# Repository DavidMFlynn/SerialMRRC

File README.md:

# SerialMRRC
 Serial Model Railroad Control

This is a set of PCBs and software to control a model railroad with RS485 data buss.

# Stand Alone Boards
Controller Board, PIC15F15345, 1KB Ram, 224B Flash, 8KW Program memory
Switch Machine, 1 servo, 1 DPDT relay
Switch Machine and Signals, 1 servo, 1 DPDT relay, 5 Signal heads

# Daughter Cards
USB Daughter Board
Input 32 Daughter Bouad, 32 Pull-to-Ground inputs
Output 32 Daughter Board, 32 Open collector Pull-to-Ground outputs
Lighting 8x Transistot Outputs, +12v resistor current limited outputs

Anamation Controller, 8 servos
Block Detector, detects voltage across diode/resistor
Optical Detector, broken beam or reflected beam

# USB Operation
 When a command packet is received from RX2 (USB):
  Source=Master, Destination=Me: Parse and Process the command.
    Send any requested data back to Master on TX2 (USB).
  Source=Master, Destination<>Me: Retransmit on TX1 (RS485)

 When a command packet is received from RX1 (RS485):
  Source=any, Destination=Me: Parse and Process the command. 
     Send any requested data back to the sender on TX1 (RS485).
  Source=any, Destination=Master: Retransmit on TX2 (USB)
  Source=any, Destination= other than Master or Me do nothing.

# Node (w/o USB)
 When a command packet is received from RX1 (RS485):
  Source=any, Destination=Me: Parse and Process the command. 
     Send any requested data back to the sender on TX1 (RS485).
  Source=any, Destination<>Me do nothing.

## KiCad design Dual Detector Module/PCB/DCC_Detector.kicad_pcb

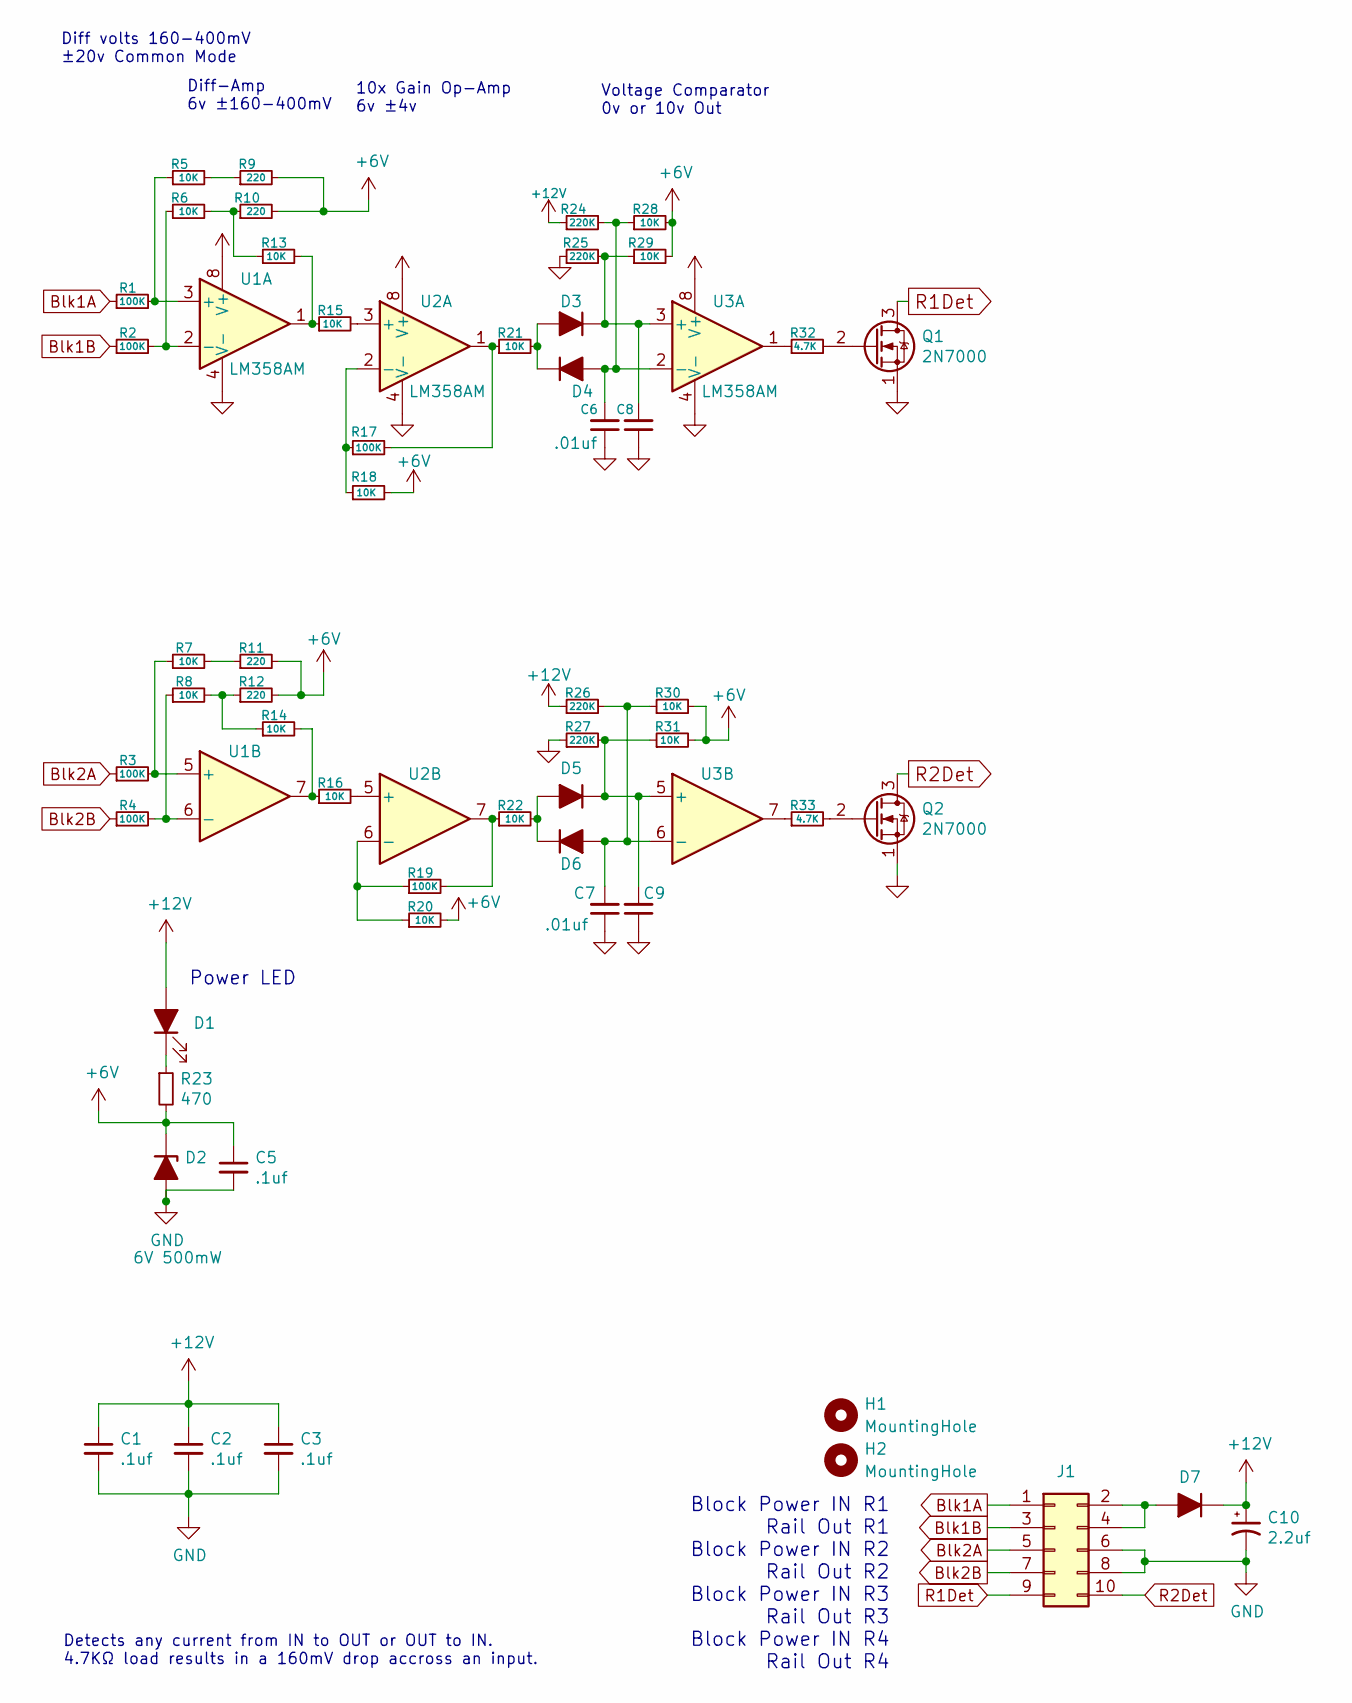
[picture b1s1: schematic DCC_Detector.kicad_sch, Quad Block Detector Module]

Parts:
C1, C2, C3, C5: .1uf; C_0805_2012Metric_Pad1.18x1.45mm_HandSolder
C6, C7, C8, C9: .01uf; C_0805_2012Metric_Pad1.18x1.45mm_HandSolder
C10: 2.2uf; CP_Elec_3x5.3
D1: 1206 LED; LED_1206_3216Metric_Pad1.42x1.75mm_HandSolder
D2: 6V 500mW; D_SMA_Handsoldering
D3, D4, D5, D6: 1N4148W; D_SOD-123
D7: D_ALT; D_SMA_Handsoldering
H1, H2: MountingHole; MountingHole_3.2mm_M3
J1: Conn_02x05_Odd_Even; PinSocket_2x05_P2.54mm_Vertical
Q1, Q2: 2N7000; TO-92_Inline
R1, R2, R3, R4, R17, R19: 100K; R_0805_2012Metric_Pad1.20x1.40mm_HandSolder
R5, R6, R7, R8, R13, R14, R15, R16, R18, R20, R21, R22, R28, R29, R30, R31: 10K; R_0805_2012Metric_Pad1.20x1.40mm_HandSolder
R9, R10, R11, R12: 220; R_0805_2012Metric_Pad1.20x1.40mm_HandSolder
R23: 470; R_0805_2012Metric_Pad1.20x1.40mm_HandSolder
R24, R25, R26, R27: 220K; R_0805_2012Metric_Pad1.20x1.40mm_HandSolder
R32, R33: 4.7K; R_0805_2012Metric_Pad1.20x1.40mm_HandSolder
U1, U2, U3: LM358AM; SOIC-8_3.9x4.9mm_P1.27mm

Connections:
+6V: C5.1, D2.1 (K), R9.2, R10.2, R11.2, R12.2, R18.2, R20.2, R23.2, R28.2, R29.2, R30.2, R31.2
+12V: C1.1, C2.1, C3.1, C10.1, D1.2 (A), D7.1 (K), R24.1, R26.1, U1.8 (V+), U2.8 (V+), U3.8 (V+)
Blk1A: J1.1, R1.1
Blk1B: J1.3, R2.1
Blk2A: J1.5, R3.1
Blk2B: J1.7, R4.1
GND: C1.2, C2.2, C3.2, C5.2, C6.1, C7.1, C8.1, C9.1, C10.2, D2.2 (A), J1.6, J1.8, Q1.1 (S), Q2.1 (S), R25.1, R27.1, U1.4 (V-), U2.4 (V-), U3.4 (V-)
unnamed: D1.1 (K), R23.1
unnamed: D3.2 (A), D4.1 (K), R21.2
unnamed: C8.2, D3.1 (K), R25.2, R29.1, U3.3 (+)
unnamed: C6.2, D4.2 (A), R24.2, R28.1, U3.2 (-)
unnamed: D5.2 (A), D6.1 (K), R22.2
unnamed: C9.2, D5.1 (K), R27.2, R31.1, U3.5 (+)
unnamed: C7.2, D6.2 (A), R26.2, R30.1, U3.6 (-)
unnamed: D7.2 (A), J1.2, J1.4
unnamed: Q1.2 (G), R32.2
unnamed: Q2.2 (G), R33.2
unnamed: R5.2, R9.1
unnamed: R6.2, R10.1, R13.1
unnamed: R7.2, R11.1
unnamed: R8.2, R12.1, R14.1
unnamed: R13.2, R15.1, U1.1
unnamed: R14.2, R16.1, U1.7
unnamed: R17.2, R21.1, U2.1
unnamed: R19.2, R22.1, U2.7
unnamed: R32.1, U3.1
unnamed: R33.1, U3.7
unnamed: R1.2, R5.1, U1.3 (+)
unnamed: R2.2, R6.1, U1.2 (-)
unnamed: R3.2, R7.1, U1.5 (+)
unnamed: R4.2, R8.1, U1.6 (-)
unnamed: R15.2, U2.3 (+)
unnamed: R17.1, R18.1, U2.2 (-)
unnamed: R16.2, U2.5 (+)
unnamed: R19.1, R20.1, U2.6 (-)
R1Det: J1.9, Q1.3 (D)
R2Det: J1.10, Q2.3 (D)

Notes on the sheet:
Detects any current from IN to OUT or OUT to IN. 4.7KΩ load results in a 160mV drop accross an input.
Voltage Comparator 0v or 10v Out
Block Power IN R1 Rail Out R1 Block Power IN R2 Rail Out R2 Block Power IN R3 Rail Out R3 Block Power IN R4 Rail Out R4
Diff-Amp 6v ±160-400mV
10x Gain Op-Amp 6v ±4v
Diff volts 160-400mV ±20v Common Mode
Power LED

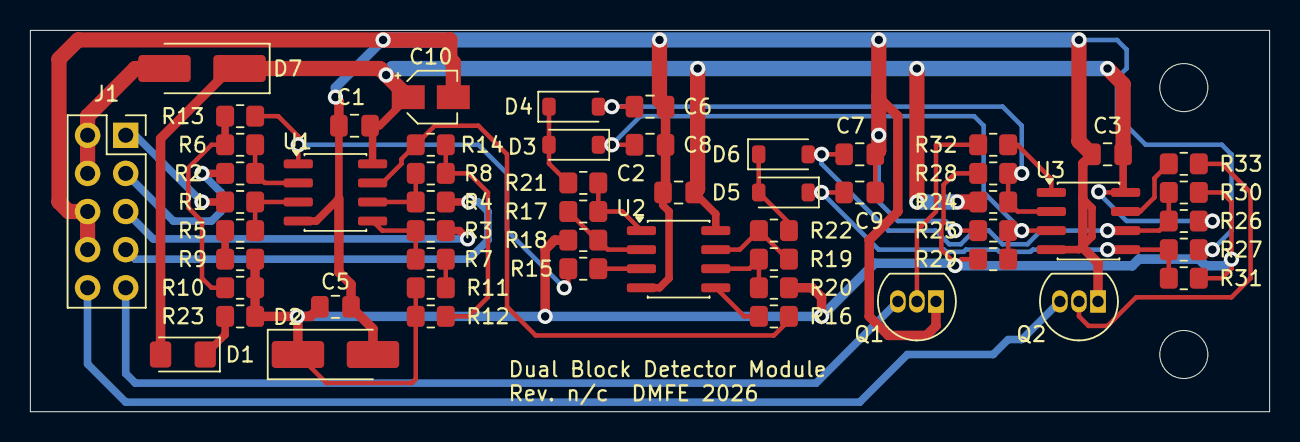
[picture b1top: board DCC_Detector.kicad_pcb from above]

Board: 2 copper layers, 82.6 x 25.4 mm, 57 parts (0 on the bottom side), 37 nets.

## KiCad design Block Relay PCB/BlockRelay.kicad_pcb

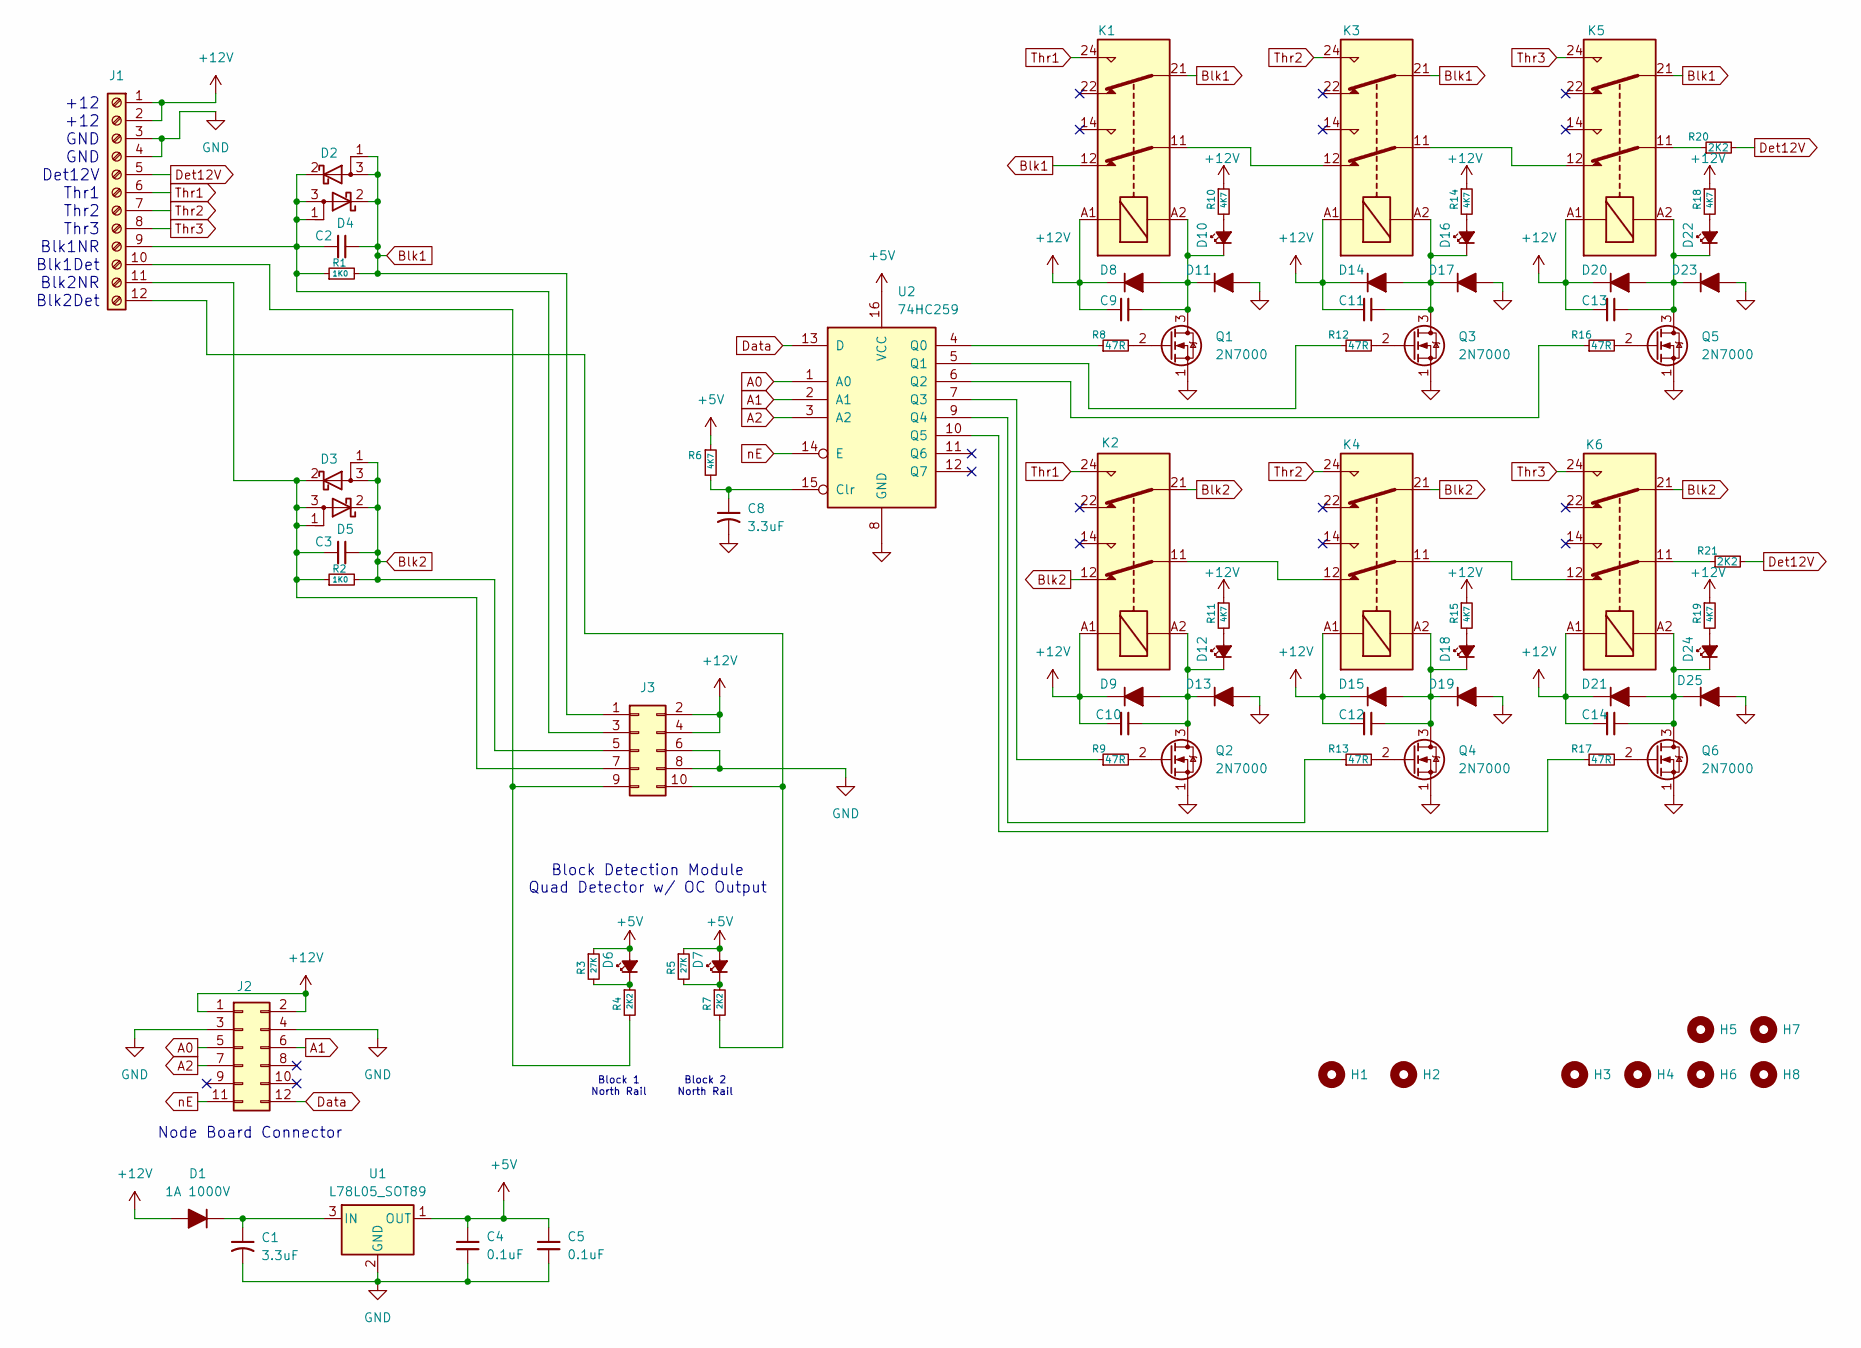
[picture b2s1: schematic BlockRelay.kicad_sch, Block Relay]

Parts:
C1, C8: 3.3uF; C_Radial_D5.0mm_H5.0mm_P2.00mm
C2, C3, C4, C5, C9, C10, C11, C12, C13, C14: 0.1uF; C_0805_2012Metric_Pad1.18x1.45mm_HandSolder
D1, D8, D9, D11, D13, D14, D15, D17, D19, D20, D21, D23, D25: 1A 1000V; D_SMA_Handsoldering
D2, D3, D4, D5: Schottky_AKA DPAK; TO-252-2
D6, D7, D10, D12, D16, D18, D22, D24: Yellow LED; LED_1206_3216Metric_Pad1.42x1.75mm_HandSolder
H1, H2, H3, H4, H5, H6, H7, H8: MountingHole; MountingHole_3.2mm_M3
J1: Screw_Terminal_01x12; TerminalBlock_Phoenix_PT-1,5-12-3.5-H_1x12_P3.50mm_Horizont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
J2: Conn_02x06_Odd_Even; PinHeader_2x06_P2.54mm_Vertical
J3: Conn_02x05_Odd_Even; PinSocket_2x05_P2.54mm_Vertical
K1, K2, K3, K4, K5, K6: Relay_DPDT; Relay_DPDT_Finder_40.52
Q1, Q2, Q3, Q4, Q5, Q6: 2N7000; TO-92_Inline
R1, R2: 1K0; R_0805_2012Metric_Pad1.20x1.40mm_HandSolder
R3, R5: 27K; R_0805_2012Metric_Pad1.20x1.40mm_HandSolder
R4, R7: 2K2; R_0805_2012Metric_Pad1.20x1.40mm_HandSolder
R6, R10, R11, R14, R15, R18, R19: 4K7; R_0805_2012Metric_Pad1.20x1.40mm_HandSolder
R8, R9, R12, R13, R16, R17: 47R; R_0805_2012Metric_Pad1.20x1.40mm_HandSolder
R20, R21: 2K2; R_Axial_DIN0516_L15.5mm_D5.0mm_P20.32mm_Horizontal
U1: L78L05_SOT89; SOT-89-3
U2: 74HC259; SOIC-16_3.9x9.9mm_P1.27mm

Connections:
+5V: C4.1, C5.1, D6.2 (A), D7.2 (A), R3.1, R5.1, R6.1, U1.1 (OUT), U2.16 (VCC)
+12V: C9.1, C10.1, C11.1, C12.1, C13.1, C14.1, D1.2 (A), D8.1 (K), D9.1 (K), D14.1 (K), D15.1 (K), D20.1 (K), D21.1 (K), J1.1, J1.2, J2.1, J2.2, J3.2, J3.4, K1.A1, K2.A1, K3.A1, K4.A1, K5.A1, K6.A1, R10.1, R11.1, R14.1, R15.1, R18.1, R19.1
A0: J2.5, U2.1 (A0)
A1: J2.6, U2.2 (A1)
A2: J2.7, U2.3 (A2)
Blk1: C2.2, D2.1 (A), D2.3 (A), D4.2 (K), J3.1, K1.12, K1.21, K3.21, K5.21, R1.2
Blk2: C3.2, D3.1 (A), D3.3 (A), D5.2 (K), J3.5, K2.12, K2.21, K4.21, K6.21, R2.2
Data: J2.12, U2.13 (D)
Det12V: J1.5, R20.2, R21.2
GND: C1.2, C4.2, C5.2, C8.2, D11.2 (A), D13.2 (A), D17.2 (A), D19.2 (A), D23.2 (A), D25.2 (A), J1.3, J1.4, J2.3, J2.4, J3.6, J3.8, Q1.1 (S), Q2.1 (S), Q3.1 (S), Q4.1 (S), Q5.1 (S), Q6.1 (S), U1.2 (GND), U2.8 (GND)
unnamed: C1.1, D1.1 (K), U1.3 (IN)
unnamed: C2.1, D2.2 (K), D4.1 (A), D4.3 (A), J1.9, J3.3, R1.1
unnamed: C3.1, D3.2 (K), D5.1 (A), D5.3 (A), J1.11, J3.7, R2.1
unnamed: D6.1 (K), R3.2, R4.1
unnamed: D7.1 (K), R5.2, R7.1
unnamed: D10.2 (A), R10.2
unnamed: C9.2, D8.2 (A), D10.1 (K), D11.1 (K), K1.A2, Q1.3 (D)
unnamed: D12.2 (A), R11.2
unnamed: C10.2, D9.2 (A), D12.1 (K), D13.1 (K), K2.A2, Q2.3 (D)
unnamed: C11.2, D14.2 (A), D16.1 (K), D17.1 (K), K3.A2, Q3.3 (D)
unnamed: C12.2, D15.2 (A), D18.1 (K), D19.1 (K), K4.A2, Q4.3 (D)
unnamed: D16.2 (A), R14.2
unnamed: D18.2 (A), R15.2
unnamed: C13.2, D20.2 (A), D22.1 (K), D23.1 (K), K5.A2, Q5.3 (D)
unnamed: C14.2, D21.2 (A), D24.1 (K), D25.1 (K), K6.A2, Q6.3 (D)
unnamed: D22.2 (A), R18.2
unnamed: D24.2 (A), R19.2
unnamed: J1.10, J3.9, R4.2
unnamed: J1.12, J3.10, R7.2
unnamed: K1.11, K3.12
unnamed: K2.11, K4.12
unnamed: K3.11, K5.12
unnamed: K4.11, K6.12
unnamed: K5.11, R20.1
unnamed: K6.11, R21.1
unnamed: Q1.2 (G), R8.2
unnamed: Q2.2 (G), R9.2
unnamed: Q3.2 (G), R12.2
unnamed: Q4.2 (G), R13.2
unnamed: Q5.2 (G), R16.2
unnamed: Q6.2 (G), R17.2
unnamed: C8.1, R6.2, U2.15 (Clr)
unnamed: R8.1, U2.4 (Q0)
unnamed: R12.1, U2.5 (Q1)
unnamed: R16.1, U2.6 (Q2)
unnamed: R9.1, U2.7 (Q3)
unnamed: R13.1, U2.9 (Q4)
unnamed: R17.1, U2.10 (Q5)
Thr1: J1.6, K1.24, K2.24
Thr2: J1.7, K3.24, K4.24
Thr3: J1.8, K5.24, K6.24
nE: J2.11, U2.14 (E)

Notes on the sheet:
Block Detection Module Quad Detector w/ OC Output
+12 +12 GND GND Det12V Thr1 Thr2 Thr3 Blk1NR Blk1Det Blk2NR Blk2Det
Block 2 North Rail
Node Board Connector
Block 1 North Rail

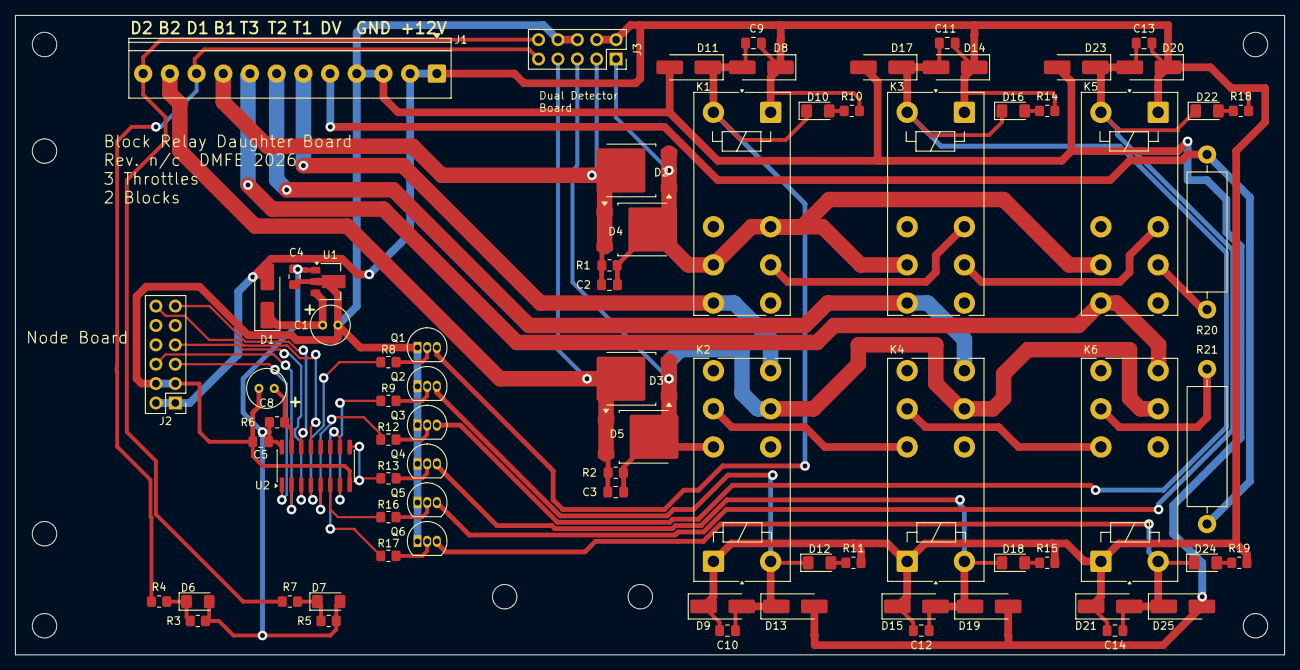
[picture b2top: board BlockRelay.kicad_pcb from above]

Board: 2 copper layers, 166.4 x 83.8 mm, 83 parts (0 on the bottom side), 52 nets.

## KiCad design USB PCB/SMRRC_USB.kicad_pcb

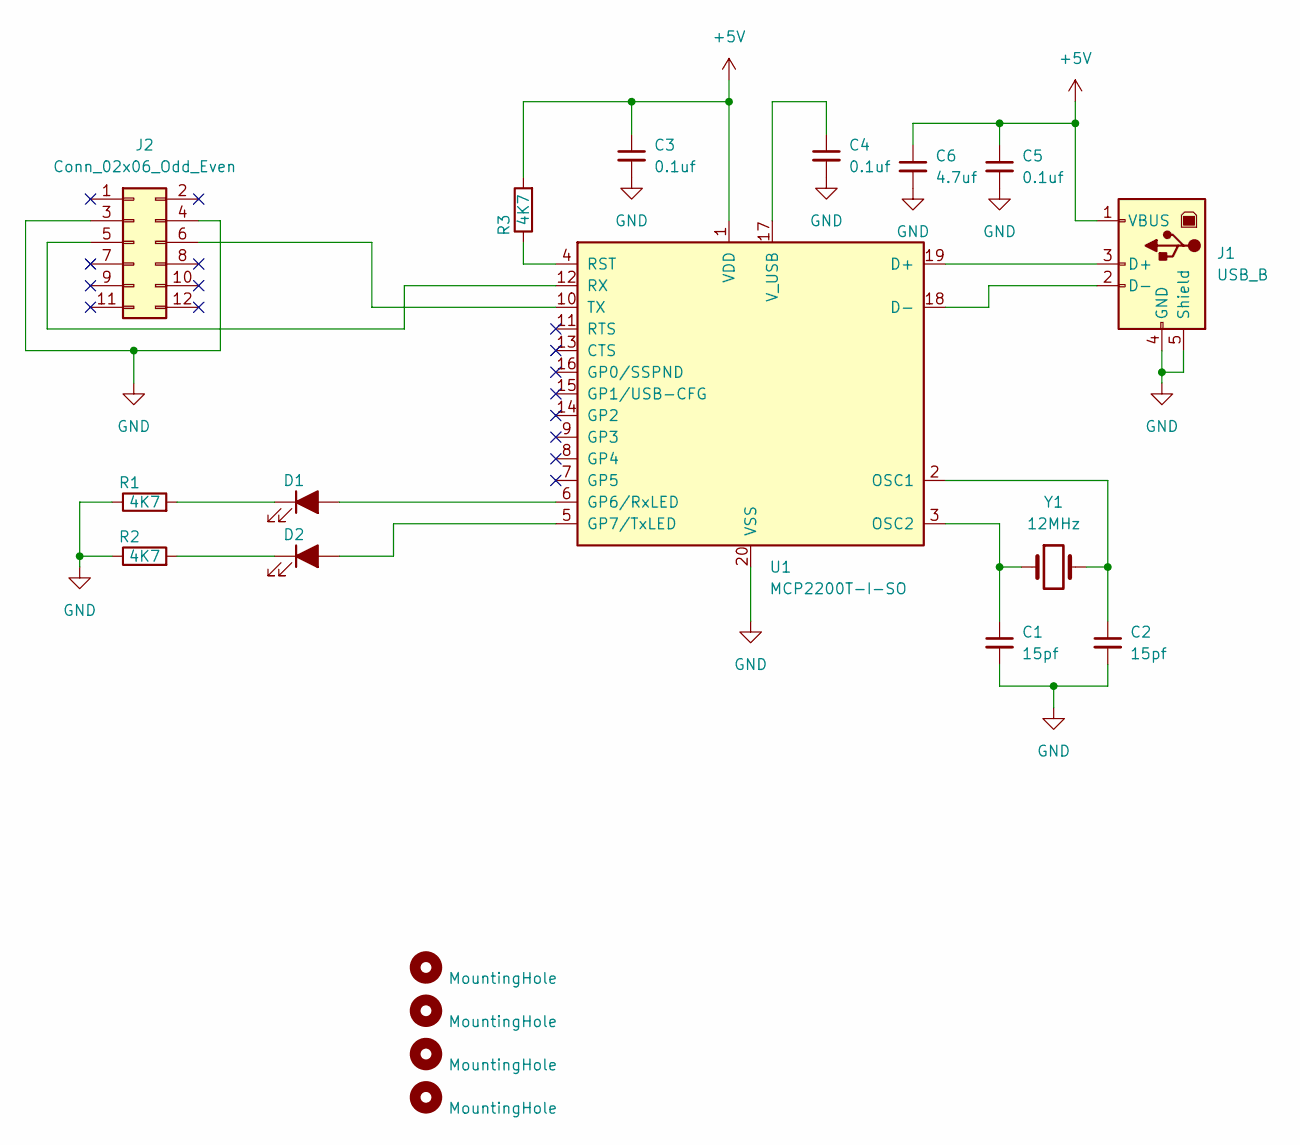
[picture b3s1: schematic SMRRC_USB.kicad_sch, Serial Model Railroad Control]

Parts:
C1, C2: 15pf; C_0805_2012Metric_Pad1.18x1.45mm_HandSolder
C3, C4, C5: 0.1uf; C_0805_2012Metric_Pad1.18x1.45mm_HandSolder
C6: 4.7uf; C_0805_2012Metric_Pad1.18x1.45mm_HandSolder
D1, D2: Green; LED_1206_3216Metric_Pad1.42x1.75mm_HandSolder
H1, H2, H3, H4: MountingHole; MountingHole_3.2mm_M3
J1: USB_B; USB_B_OST_USB-B1HSxx_Horizontal
J2: Conn_02x06_Odd_Even; PinHeader_2x06_P2.54mm_Vertical
R1, R2, R3: 4K7; R_0805_2012Metric_Pad1.20x1.40mm_HandSolder
U1: MCP2200T-I-SO; SOIC-20W_7.5x12.8mm_P1.27mm
Y1: 12MHz; Crystal_HC49-4H_Vertical

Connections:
+5V: C3.1, C5.1, C6.1, J1.1 (VBUS), R3.2, U1.1 (VDD)
GND: C1.2, C2.2, C3.2, C4.2, C5.2, C6.2, J1.4 (GND), J1.5 (Shield), J2.3, J2.4, R1.1, R2.1, U1.20 (VSS)
unnamed: D1.2 (A), U1.6 (GP6/RxLED)
unnamed: D1.1 (K), R1.2
unnamed: D2.2 (A), U1.5 (GP7/TxLED)
unnamed: D2.1 (K), R2.2
unnamed: J1.3 (D+), U1.19 (D+)
unnamed: J1.2 (D-), U1.18 (D-)
unnamed: J2.5, U1.12 (RX)
unnamed: J2.6, U1.10 (TX)
unnamed: C2.1, U1.2 (OSC1), Y1.2
unnamed: C1.1, U1.3 (OSC2), Y1.1
unnamed: R3.1, U1.4 (RST)
unnamed: C4.1, U1.17 (V_USB)

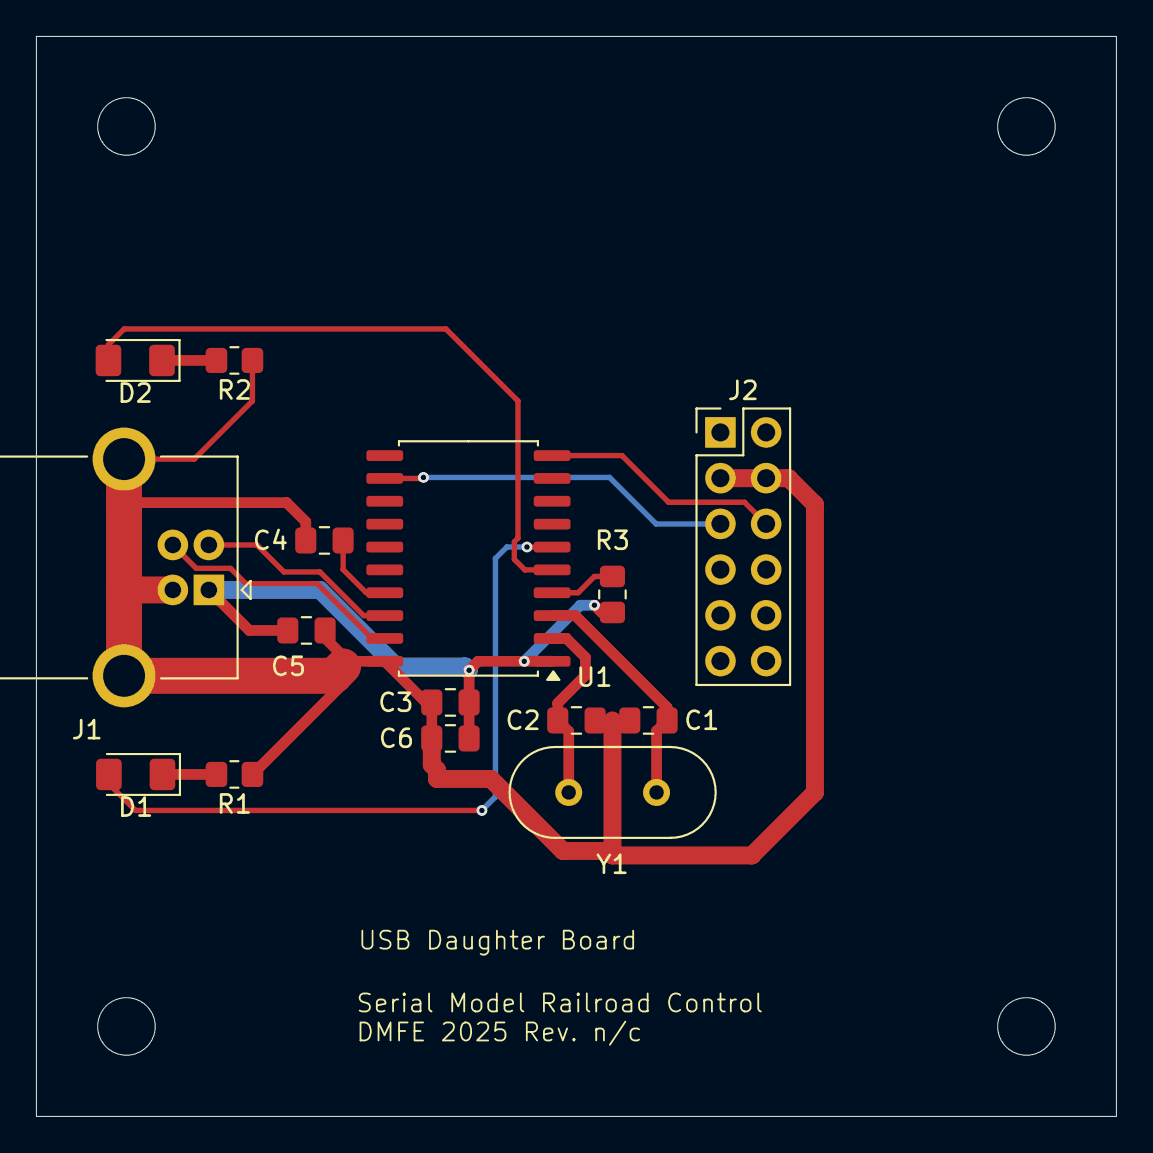
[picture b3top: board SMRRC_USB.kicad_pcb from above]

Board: 2 copper layers, 60.0 x 60.0 mm, 19 parts (0 on the bottom side), 14 nets.

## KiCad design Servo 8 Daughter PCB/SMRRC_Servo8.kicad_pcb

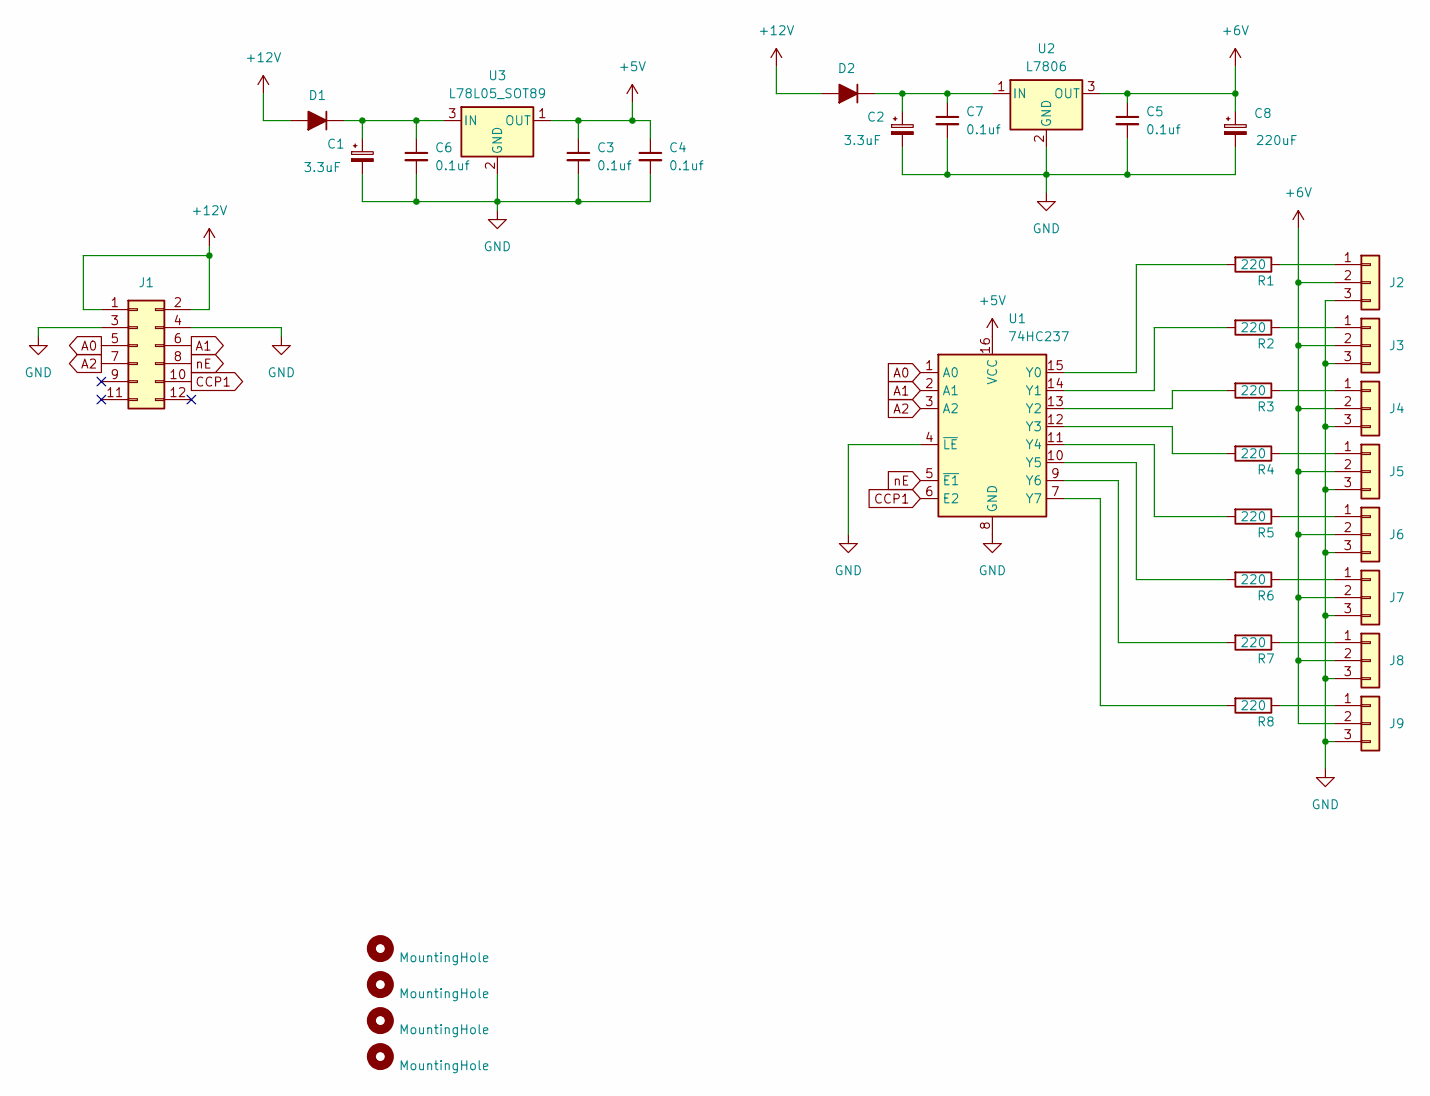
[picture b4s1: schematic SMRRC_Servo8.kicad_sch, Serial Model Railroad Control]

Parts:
C1, C2: 3.3uF; CP_Radial_D5.0mm_P2.00mm
C3, C4, C5, C6, C7: 0.1uf; C_0805_2012Metric_Pad1.18x1.45mm_HandSolder
C8: 220uF; CP_Radial_D6.3mm_P2.50mm
D1: SMA; D_SMA_Handsoldering
D2: SMB; D_SMB_Handsoldering
H1, H2, H3, H4: MountingHole; MountingHole_3.2mm_M3
J1: Conn_02x06_Odd_Even; PinHeader_2x06_P2.54mm_Vertical
J2, J3, J4, J5, J6, J7, J8, J9: Conn_01x03; PinHeader_1x03_P2.54mm_Horizontal
R1, R2, R3, R4, R5, R6, R7, R8: 220; R_0805_2012Metric_Pad1.20x1.40mm_HandSolder
U1: 74HC237; SOIC-16_3.9x9.9mm_P1.27mm
U2: L7806; TO-263-2
U3: L78L05_SOT89; SOT-89-3

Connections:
+5V: C3.1, C4.1, U1.16 (VCC), U3.1 (OUT)
+6V: C5.1, C8.1, J2.2, J3.2, J4.2, J5.2, J6.2, J7.2, J8.2, J9.2, U2.3 (OUT)
+12V: D1.2 (A), D2.2 (A), J1.1, J1.2
A0: J1.5, U1.1 (A0)
A1: J1.6, U1.2 (A1)
A2: J1.7, U1.3 (A2)
CCP1: J1.10, U1.6 (E2)
GND: C1.2, C2.2, C3.2, C4.2, C5.2, C6.2, C7.2, C8.2, J1.3, J1.4, J2.3, J3.3, J4.3, J5.3, J6.3, J7.3, J8.3, J9.3, U1.4 (~LE), U1.8 (GND), U2.2 (GND), U3.2 (GND)
unnamed: C1.1, C6.1, D1.1 (K), U3.3 (IN)
unnamed: C2.1, C7.1, D2.1 (K), U2.1 (IN)
unnamed: J2.1, R1.1
unnamed: J3.1, R2.1
unnamed: J4.1, R3.1
unnamed: J5.1, R4.1
unnamed: J6.1, R5.1
unnamed: J7.1, R6.1
unnamed: J8.1, R7.1
unnamed: J9.1, R8.1
unnamed: R1.2, U1.15 (Y0)
unnamed: R2.2, U1.14 (Y1)
unnamed: R3.2, U1.13 (Y2)
unnamed: R4.2, U1.12 (Y3)
unnamed: R5.2, U1.11 (Y4)
unnamed: R6.2, U1.10 (Y5)
unnamed: R7.2, U1.9 (Y6)
unnamed: R8.2, U1.7 (Y7)
nE: J1.8, U1.5 (~E1)

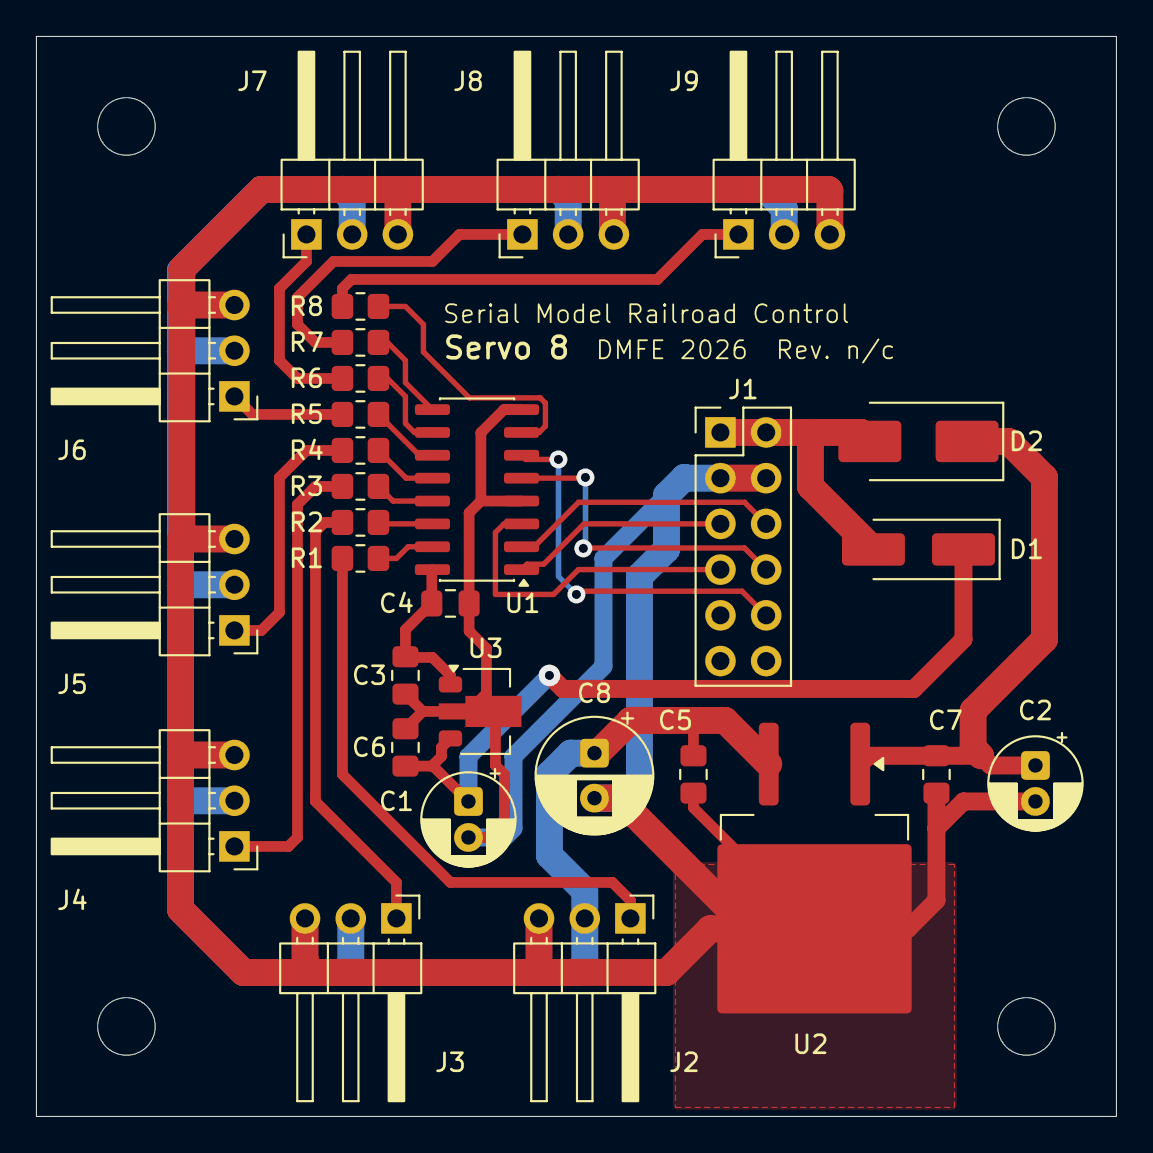
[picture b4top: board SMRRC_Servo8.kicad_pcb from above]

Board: 2 copper layers, 60.0 x 60.0 mm, 34 parts (0 on the bottom side), 27 nets.

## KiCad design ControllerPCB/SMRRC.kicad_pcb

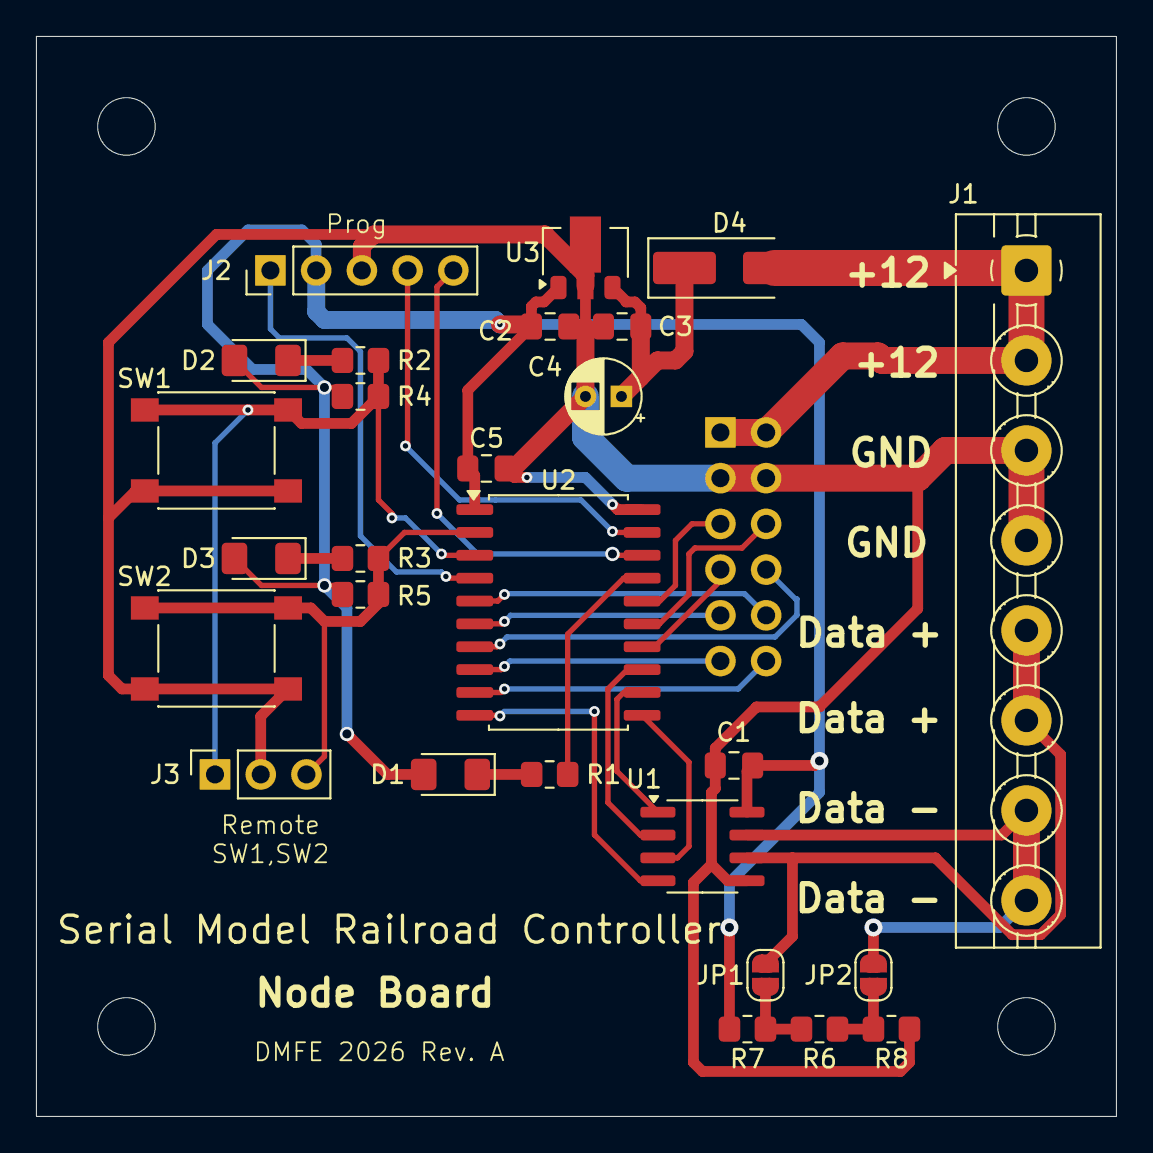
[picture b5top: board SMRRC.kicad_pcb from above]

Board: 2 copper layers, 60.0 x 60.0 mm, 32 parts (1 on the bottom side), 29 nets.

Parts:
C1, C2, C3, C5: 0.1uf; C_0805_2012Metric_Pad1.18x1.45mm_HandSolder
C4: 10uf; CP_Radial_D4.0mm_P2.00mm
D1, D2, D3: LED_Filled; D_1206_3216Metric_Pad1.42x1.75mm_HandSolder
D4: SMA; D_SMA_Handsoldering
H1, H2, H3, H4: MountingHole_3.2mm_M3
J1: Conn_01x08_Socket; TerminalBlock_MaiXu_MX126-5.0-08P_1x08_P5.00mm
J2: Conn_01x05; PinHeader_1x05_P2.54mm_Vertical
J3: Conn_01x03; PinSocket_1x03_P2.54mm_Vertical
J4: Conn_02x06_Odd_Even; PinSocket_2x06_P2.54mm_Vertical
JP1, JP2: Jumper_2_Open; SolderJumper-2_P1.3mm_Open_RoundedPad1.0x1.5mm
R1, R2, R3: 1K0; R_0805_2012Metric_Pad1.20x1.40mm_HandSolder
R4, R5: 47K; R_0805_2012Metric_Pad1.20x1.40mm_HandSolder
R6: 120; R_0805_2012Metric_Pad1.20x1.40mm_HandSolder
R7, R8: 10K; R_0805_2012Metric_Pad1.20x1.40mm_HandSolder
SW1, SW2: SW_Push; SW_SPST_PTS645
U1: THVD1500; SOIC-8_3.9x4.9mm_P1.27mm
U2: PIC16F15345-I/SO; SOIC-20W_7.5x12.8mm_P1.27mm
U3: L78L05_SOT89; SOT-89-3

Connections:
+5V: C1.1, C2.1, C5.1, D1.2 (A), D2.2 (A), D3.2 (A), J2.2, R4.1, R5.1, R7.2, U1.8 (VCC), U2.1 (VDD), U3.1 (OUT)
+12V: D4.2 (A), J1.1, J1.2, J4.1, J4.2
GND: C1.2, C2.2, C3.2, C4.2, C5.2, J1.3, J1.4, J2.3, J3.2, J4.3, J4.4, R8.1, SW1.1, SW2.1, U1.5 (GND), U2.20 (VSS), U3.2 (GND)
unnamed: D1.1 (K), R1.1
unnamed: D2.1 (K), R2.1
unnamed: D3.1 (K), R3.1
unnamed: C3.1, C4.1, D4.1 (K), U3.3 (IN)
unnamed: J1.5, J1.6, JP1.1 (A), U1.6 (A)
unnamed: J1.7, J1.8, JP2.1 (A), U1.7 (B)
unnamed: J2.1, U2.4 (RA3/~MCLR/VPP)
unnamed: J2.4, U2.19 (RA0/ICSPDAT)
unnamed: J2.5, U2.18 (RA1/ICSPCLK)
unnamed: J3.1, R2.2, R4.2, SW1.2, U2.3 (RA4)
unnamed: J3.3, R3.2, R5.2, SW2.2, U2.2 (RA5)
unnamed: J4.5, U2.16 (RC0)
unnamed: J4.6, U2.15 (RC1)
unnamed: J4.7, U2.14 (RC2)
unnamed: J4.8, U2.7 (RC3)
unnamed: J4.9, U2.6 (RC4)
unnamed: J4.10, U2.5 (RC5)
unnamed: J4.11, U2.8 (RC6)
unnamed: J4.12, U2.9 (RC7)
unnamed: JP1.2 (B), R6.2, R7.1
unnamed: JP2.2 (B), R6.1, R8.2
unnamed: U1.3 (DE), U2.11 (RB6)
unnamed: U1.4 (DI), U2.10 (RB7)
unnamed: U1.1 (RO), U2.12 (RB5)
unnamed: U1.2 (~RE), U2.13 (RB4)
unnamed: R1.2, U2.17 (RA2)

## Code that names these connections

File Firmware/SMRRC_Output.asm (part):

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; uController pinout (PIC16F15345):
;
; Pin 1  (Vdd)		+5 Volts
; Pin 2  (RA5)		LED2 (Active Low Input/Output)(LED2/Button2)
; Pin 3  (RA4)		LED1 (Active Low Input/Output)(LED1/Button1)
; Pin 4  (RA3/MCLR*)		VPP/MCLR*
; Pin 5  (RC5)		I/O    Daughter Card Pin 10
; Pin 6  (RC4)		I/O    Daughter Card Pin 9
; Pin 7  (RC3)		I/O    Daughter Card Pin 8
; Pin 8  (RC6)		I/O    Daughter Card Pin 11
; Pin 9  (RC7)		I/O    Daughter Card Pin 12
; Pin 10 (RB7/TX1)		RS-485 Driver
; Pin 11 (RB6)		RS-485 Driver Enable (Active High Output)
; Pin 12 (RB5)		RS-485 Receiver
; Pin 13 (RB4)		RS-485 Receiver Enable (Active Low Output)
; Pin 14 (RC2)		I/O    Daughter Card Pin 7
; Pin 15 (RC1)		RX2 or I/O Daughter Card Pin 6
; Pin 16 (RC0)		TX2 or I/O Daughter Card Pin 5
; Pin 17 (RA2)		SYSLED (Active Low Output)(System LED)
; Pin 18 (RRA/ICSPCLK)		ICSPCLK
; Pin 19 (RA0/ICSPDAT)		ICSPDAT
; Pin 20 (Vss)		Ground
;
;=========================================================================================
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
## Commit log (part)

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2025-03-23 create repo
2025-03-23 Main Schematic
2025-03-24 packet serial intf added
2025-03-25 worked on switch machine pcb
2025-03-27 Switch and Signal
2025-03-29 signal leds
2025-03-31 Signal Head
2025-04-03 first code
2025-04-03 looking
2025-04-03 blink?
2025-04-04 finally it blinks!

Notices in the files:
Firmware/SMRRC_Output.asm:
License:	MIT License
